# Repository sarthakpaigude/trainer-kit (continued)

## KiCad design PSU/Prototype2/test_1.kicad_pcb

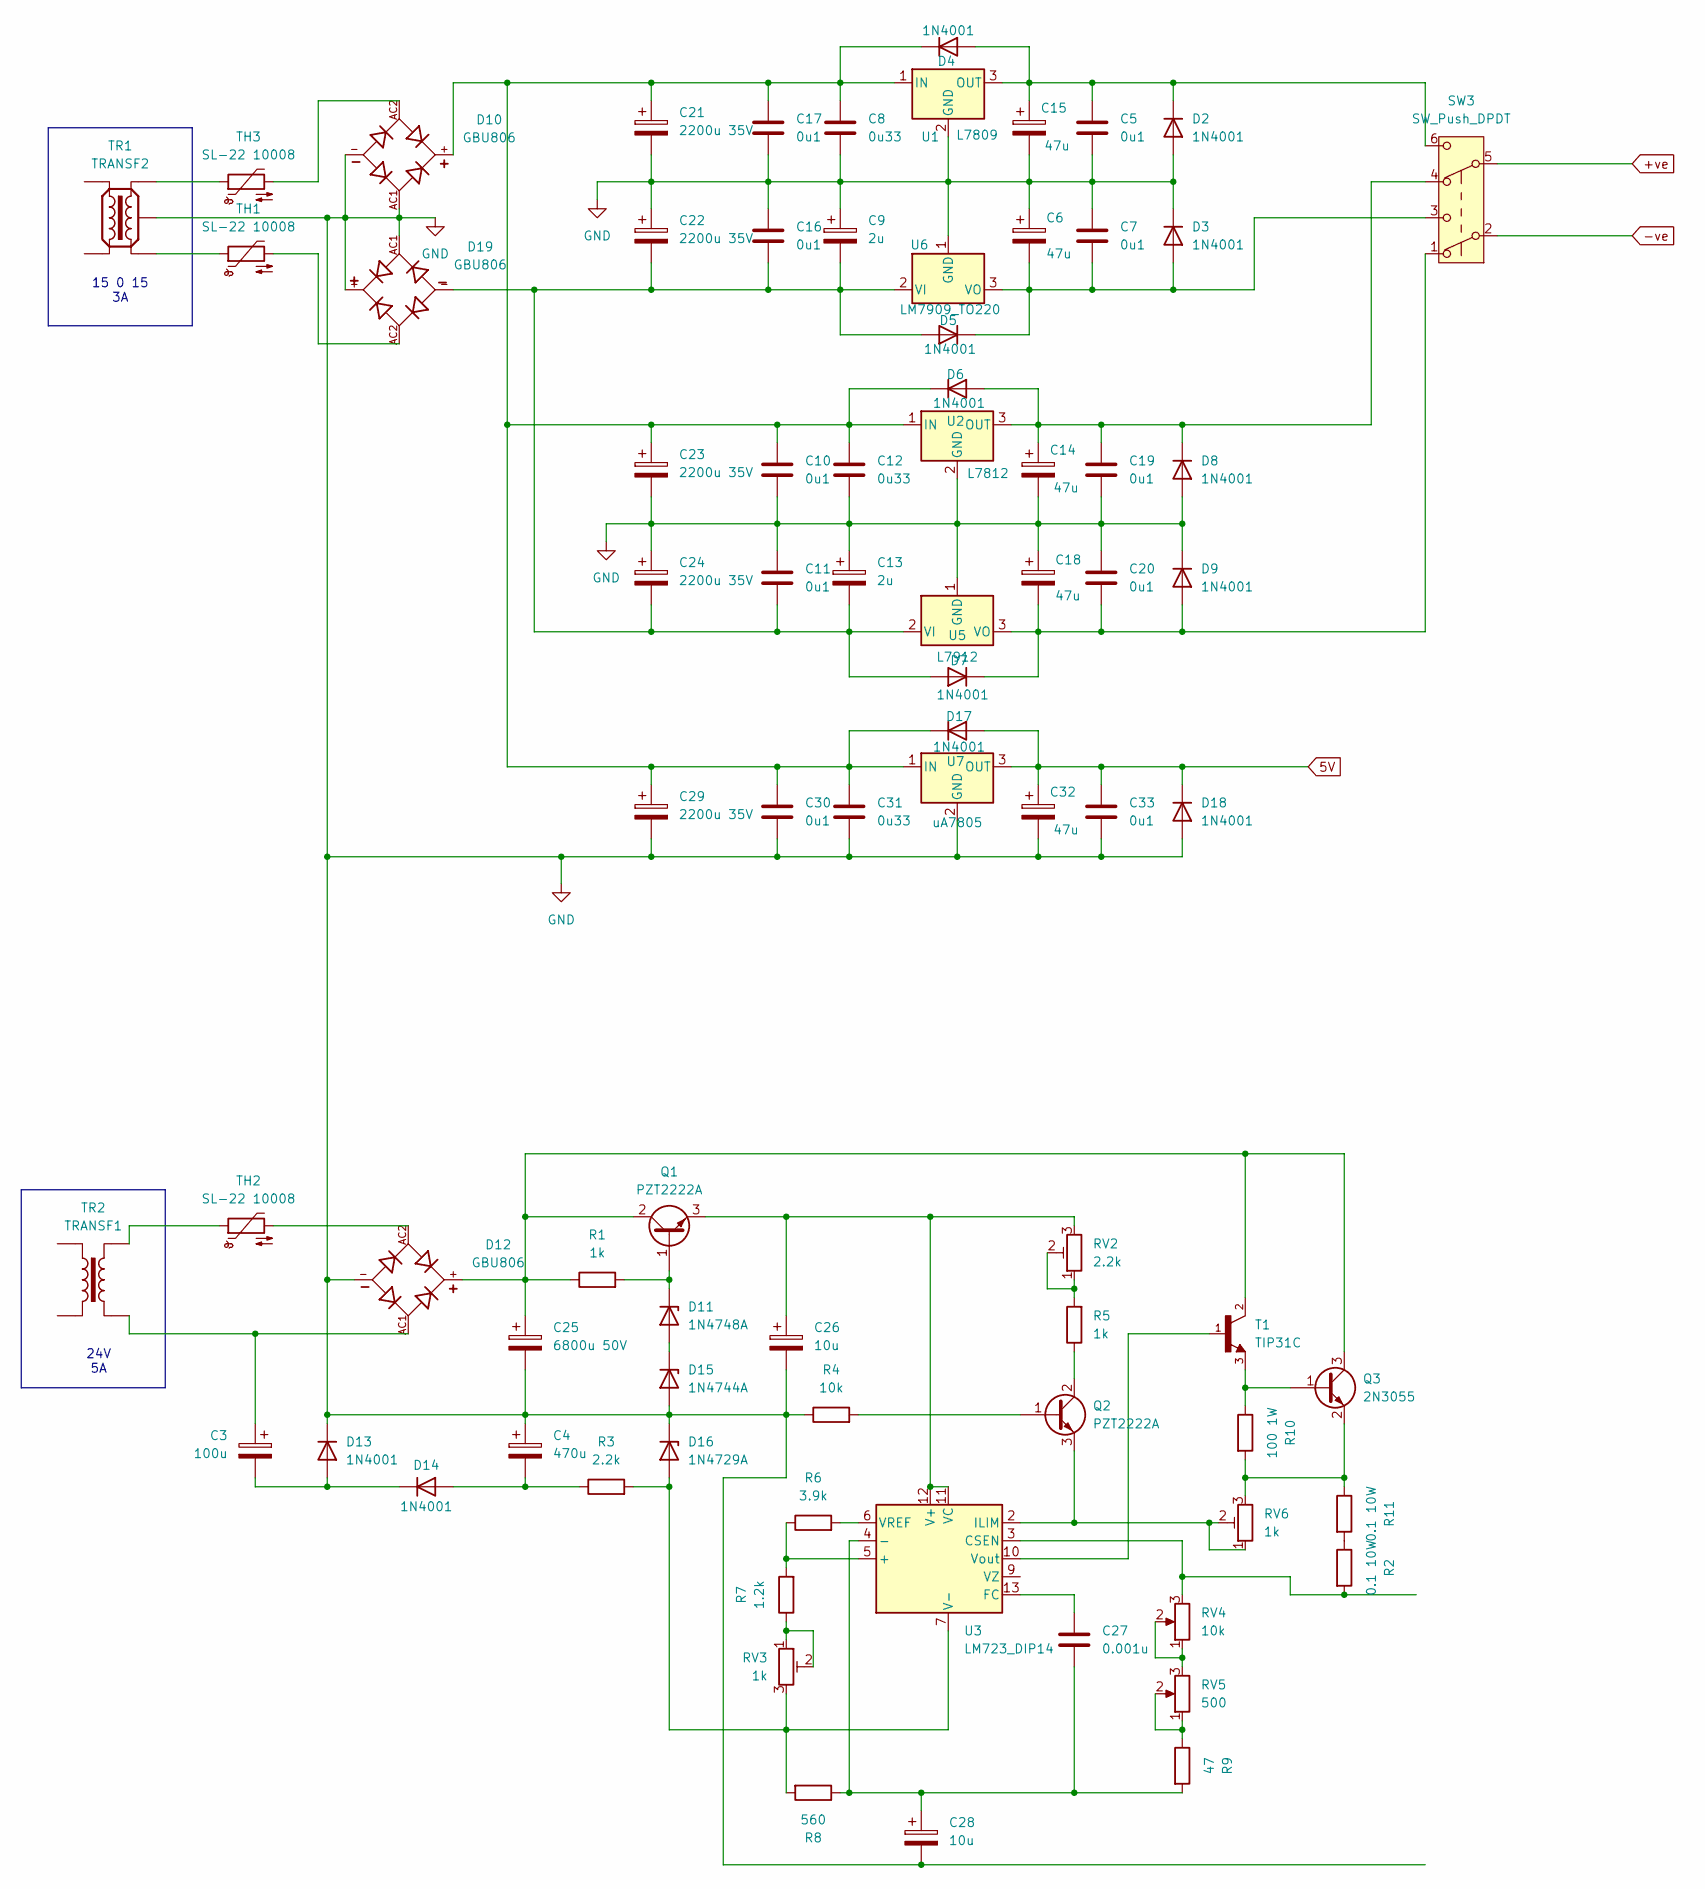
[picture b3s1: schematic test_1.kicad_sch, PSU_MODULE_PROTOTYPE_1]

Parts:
C3: 100u; CP_Radial_D8.0mm_P3.80mm
C4: 470u; CP_Radial_D12.5mm_P5.00mm
C5, C7, C10, C11, C16, C17, C19, C20, C30, C33: 0u1; C_1206_3216Metric_Pad1.33x1.80mm_HandSolder
C6, C14, C15, C18, C32: 47u; CP_Radial_D8.0mm_P3.80mm
C8, C12, C31: 0u33; C_1206_3216Metric_Pad1.33x1.80mm_HandSolder
C9, C13: 2u; CP_Radial_D8.0mm_P3.80mm
C21, C22, C23, C24, C29: 2200u 35V; CP_Radial_D22.0mm_P10.00mm_SnapIn
C25: 6800u 50V; CP_Radial_D22.0mm_P10.00mm_SnapIn
C26, C28: 10u; CP_Radial_D8.0mm_P3.80mm
C27: 0.001u; C_1206_3216Metric_Pad1.33x1.80mm_HandSolder
D2, D3, D4, D5, D6, D7, D8, D9, D13, D14, D17, D18: 1N4001; D_DO-41_SOD81_P10.16mm_Horizontal
D10, D12, D19: GBU806; SIP343W114P508L2205H2134Q4; PARTREV E2103; DigiKey_Part_Number GBU806DI-ND
D11: 1N4748A; D_DO-41_SOD81_P10.16mm_Horizontal
D15: 1N4744A; D_DO-41_SOD81_P10.16mm_Horizontal
D16: 1N4729A; D_DO-41_SOD81_P10.16mm_Horizontal
Q1, Q2: PZT2222A; SOT-223-3_TabPin2
Q3: 2N3055; TO-3
R1, R5: 1k; R_1206_3216Metric_Pad1.30x1.75mm_HandSolder
R2, R11: 0.1 10W; R_Axial_Power_L38.0mm_W9.0mm_P40.64mm
R3: 2.2k; R_1206_3216Metric_Pad1.30x1.75mm_HandSolder
R4: 10k; R_1206_3216Metric_Pad1.30x1.75mm_HandSolder
R6: 3.9k; R_1206_3216Metric_Pad1.30x1.75mm_HandSolder
R7: 1.2k; R_1206_3216Metric_Pad1.30x1.75mm_HandSolder
R8: 560; R_1206_3216Metric_Pad1.30x1.75mm_HandSolder
R9: 47; R_1206_3216Metric_Pad1.30x1.75mm_HandSolder
R10: 100 1W; R_Axial_DIN0516_L15.5mm_D5.0mm_P20.32mm_Horizontal
RV2: 2.2k; Potentiometer_Bourns_3296W_Vertical
RV3, RV6: 1k; Potentiometer_Bourns_3296W_Vertical
RV4: 10k; Potentiometer_Bourns_3296Y_Vertical
RV5: 500; Potentiometer_Bourns_3296Y_Vertical
SW3: SW_Push_DPDT
T1: TIP31C; TO-220-3_Vertical
TH1, TH2, TH3: SL-22 10008; TO-220F-2_Vertical
TR1: TRANSF2
TR2: TRANSF1
U1: L7809; TO-220-3_Vertical
U2: L7812; TO-220-3_Vertical
U3: LM723_DIP14; DIP-14_W7.62mm
U5: L7912; TO-220-3_Vertical
U6: LM7909_TO220; TO-220-3_Vertical
U7: uA7805; TO-220-3_Vertical

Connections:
5V: C32.1, C33.1, D17.2 (A), D18.1 (K), U7.3 (OUT)
GND: C4.1, C5.2, C6.1, C7.1, C8.2, C9.1, C10.2, C11.1, C12.2, C13.1, C14.2, C15.2, C16.1, C17.2, C18.1, C19.2, C20.1, C21.2, C22.1, C23.2, C24.1, C25.2, C26.2, C28.2, C29.2, C30.2, C31.2, C32.2, C33.2, D2.2 (A), D3.1 (K), D8.2 (A), D9.1 (K), D10.-, D10.AC1, D12.-, D13.1 (K), D15.2 (A), D16.1 (K), D18.2 (A), D19.+, D19.AC1, R4.1, TR1.0, U1.2 (GND), U2.2 (GND), U5.1 (GND), U6.1 (GND), U7.2 (GND)
unnamed: C3.1, D12.AC1, TR2.3
unnamed: C5.1, C15.1, D2.1 (K), D4.2 (A), SW3.6 (C), U1.3 (OUT)
unnamed: C6.2, C7.2, D3.2 (A), D5.1 (K), SW3.3 (C), U6.3 (VO)
unnamed: C9.2, C11.2, C13.2, C16.2, C22.2, C24.2, D5.2 (A), D7.2 (A), D19.-, U5.2 (VI), U6.2 (VI)
unnamed: C14.1, C19.1, D6.2 (A), D8.1 (K), SW3.4 (A), U2.3 (OUT)
unnamed: C18.2, C20.2, D7.1 (K), D9.2 (A), SW3.1 (A), U5.3 (VO)
unnamed: D10.AC2, TH3.2
unnamed: D11.2 (A), D15.1 (K)
unnamed: D11.1 (K), Q1.1 (B), R1.2
unnamed: D12.AC2, TH2.2
unnamed: C3.2, D13.2 (A), D14.1 (K)
unnamed: C4.2, D14.2 (A), R3.1
unnamed: D16.2 (A), R3.2, R8.2, RV3.3, U3.7 (V-)
unnamed: C8.1, C10.1, C12.1, C17.1, C21.1, C23.1, C29.1, C30.1, C31.1, D4.1 (K), D6.1 (K), D10.+, D17.1 (K), U1.1 (IN), U2.1 (IN), U7.1 (IN)
unnamed: D19.AC2, TH1.2
unnamed: C25.1, D12.+, Q1.2 (C), Q3.3 (C), R1.1, T1.2
unnamed: C26.1, Q1.3 (E), RV2.3, U3.11 (VC), U3.12 (V+)
unnamed: Q2.1 (B), R4.2
unnamed: Q2.2 (C), R5.1
unnamed: Q2.3 (E), RV6.1, RV6.2, U3.2 (ILIM)
unnamed: Q3.1 (B), R10.1, T1.3
unnamed: Q3.2 (E), R10.2, R11.1, RV6.3
unnamed: R5.2, RV2.1, RV2.2
unnamed: R7.1, RV3.1, RV3.2
unnamed: R9.1, RV5.1, RV5.2
unnamed: R2.1, R11.2
unnamed: RV4.1, RV4.2, RV5.3
unnamed: TH1.1, TR1.3
unnamed: TH2.1, TR2.4
unnamed: TH3.1, TR1.4
unnamed: R6.1, R7.2, U3.5 (+)
unnamed: C27.2, C28.1, R8.1, R9.2, U3.4 (-)
unnamed: R2.2, RV4.3, U3.3 (CSEN)
unnamed: C27.1, U3.13 (FC)
unnamed: R6.2, U3.6 (VREF)
unnamed: T1.1, U3.10 (Vout)

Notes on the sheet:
15 0 15 3A
24V 5A

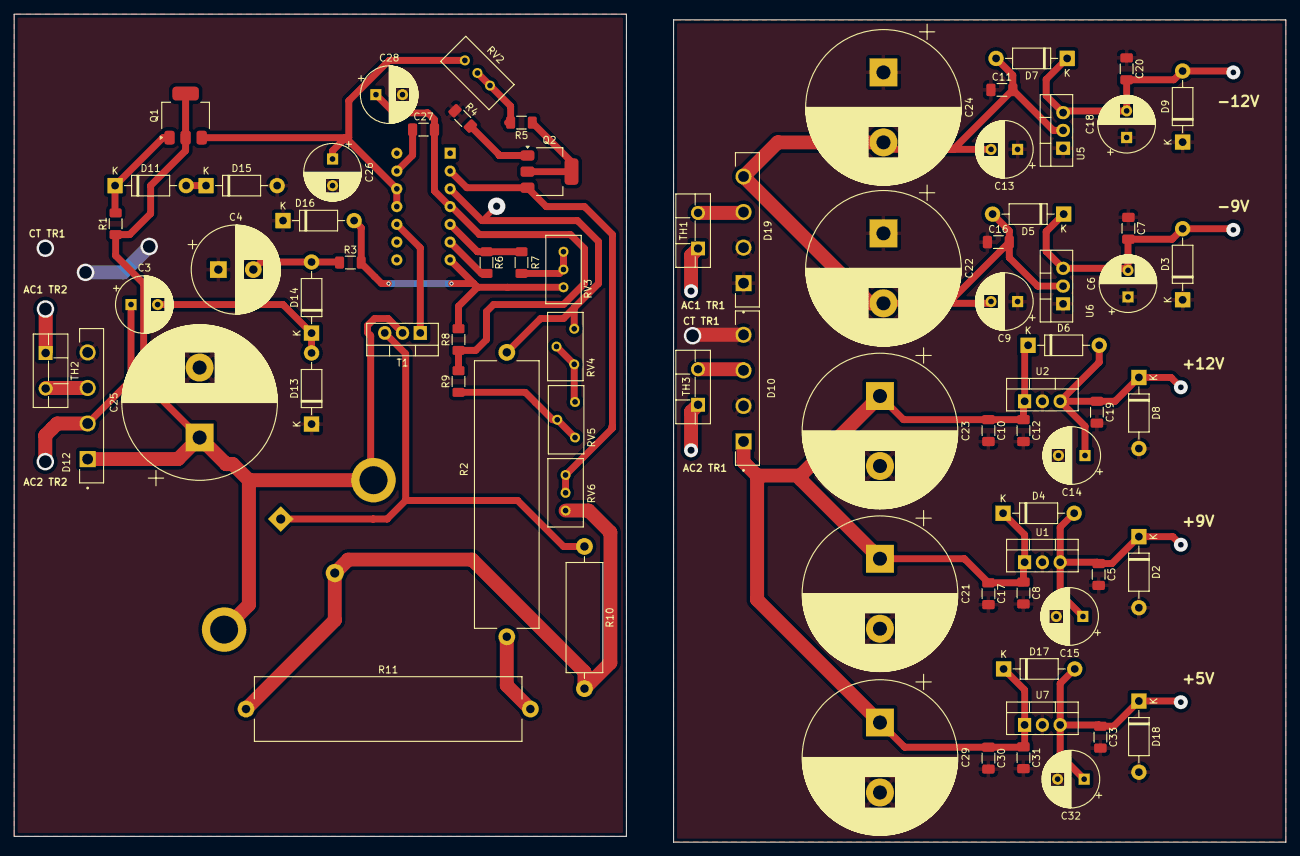
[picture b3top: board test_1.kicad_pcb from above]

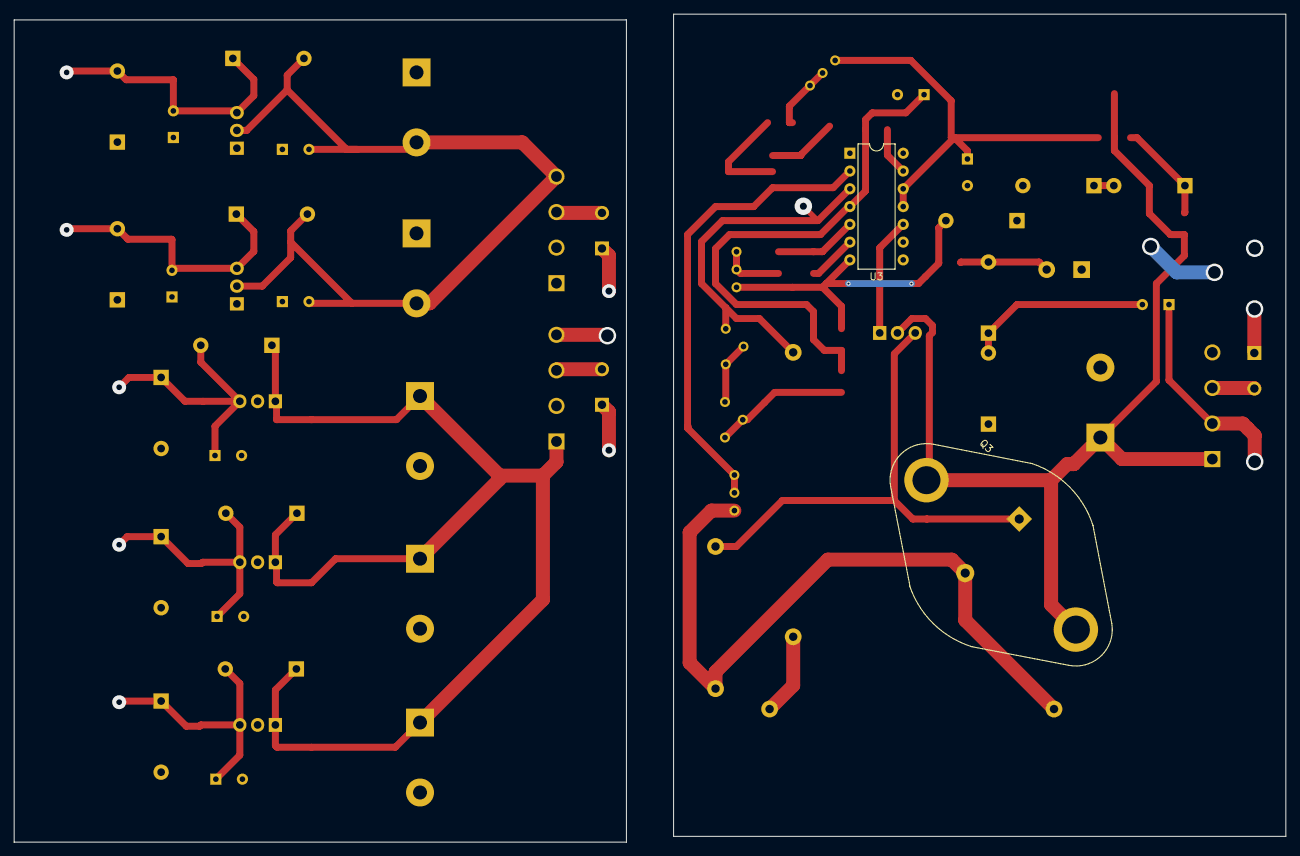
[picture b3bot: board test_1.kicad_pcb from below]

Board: 2 copper layers, 181.7 x 118.3 mm, 78 parts (2 on the bottom side), 35 nets.

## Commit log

2025-09-10 Added PCB Files for PSU
    -KiCad Files
    -Proteus Files
2025-09-10 Uploaded STM32 board
    STM32H723VET6 Breakout Board PCB design was uploaded
2026-06-05 Add files via upload
    added STM32H730IBT PCB
